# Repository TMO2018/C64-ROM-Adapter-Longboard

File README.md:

# C64-ROM-Adapter-Longboard
Flash ROM replacement for the 24 pol ROMs

The board serves for adapting a CHARACTER (U5, 4k, 2332), KERNAL (U4, 8k, 2364) or BASIC (U3, 8k, 2364) ROM to a 39SF010A (16x8k) / 39SF020A (32x8k) / 39SF040A (64x8k) 5V FLASH-ROM. The pin out of both ICs are slightly different and need adaptation. Furthermore, it allows to access different character sets (up to 32/64/128), kernals (up to 16/32/64) or basics (up to 16/32/64) or a combination of these three ROM typs which can be selected via DIP switch or/and the pin header (A12 to A18) on the module.

The pin header is connected in a way, that the selection can either be accomplished with switches or a microcontroller like an Arduino etc. 

Only one ROM-type (KERNAL or BASIC or CHARACTER) at the same time is allowed.

You can program the FLASH-ROM before soldering or with a special program adaptor after soldering. The second way allows you to reprogram the FLASH-ROM later without resoldering. On the BACK view there are the program pads JA13 to JA18, JWE1 and JOE1.

It should be possible to use the ROM-Adapter in a 1541 floppy drive with 24 pol ROMs (2364) too.

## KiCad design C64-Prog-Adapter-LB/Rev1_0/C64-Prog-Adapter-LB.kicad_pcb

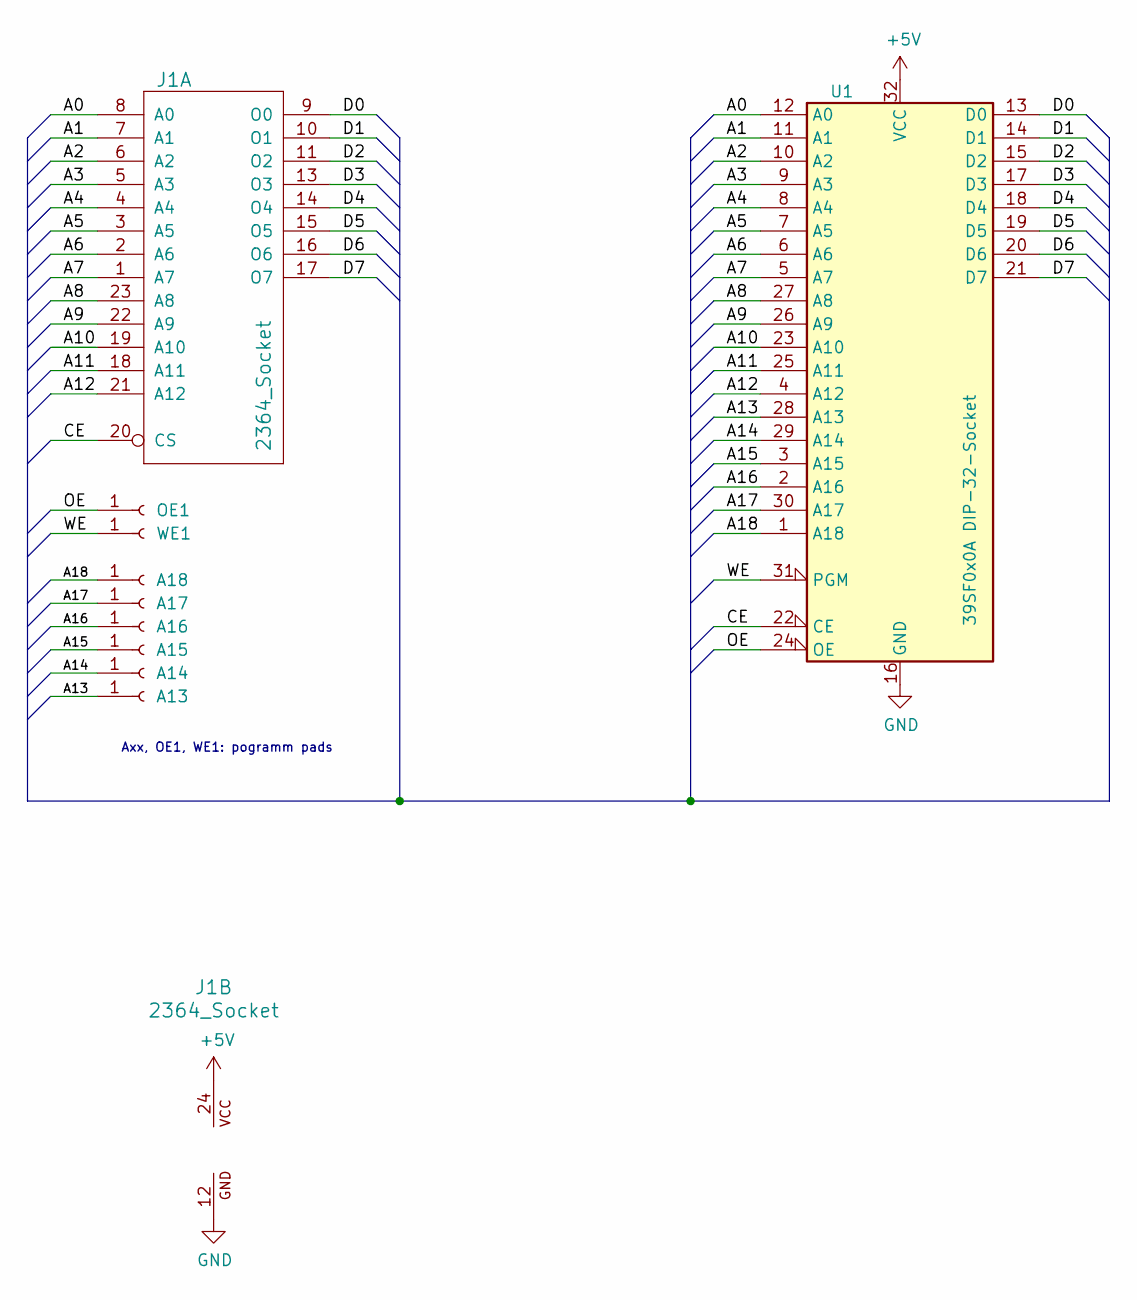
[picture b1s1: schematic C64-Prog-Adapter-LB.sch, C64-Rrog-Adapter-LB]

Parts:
A13, A14, A15, A16, A17, A18: Conn_01x01_Female; Pin_Header_Straight_1x01_Pitch2.54mm_dia1.10mm_TMO
J1: 2364_Socket; DIP-24_2332_2364_Socket
OE1: Conn_01x01_Female; Pin_Header_Straight_1x01_Pitch2.54mm_dia1.10mm_TMO
U1: 39SF0x0A DIP-32-Socket; DIP-32_W15.24mm_Socket_TMO
WE1: Conn_01x01_Female; Pin_Header_Straight_1x01_Pitch2.54mm_dia1.10mm_TMO

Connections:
+5V: J1.24 (VCC), U1.32 (VCC)
/A0: J1.8 (A0), U1.12 (A0)
/A1: J1.7 (A1), U1.11 (A1)
/A2: J1.6 (A2), U1.10 (A2)
/A3: J1.5 (A3), U1.9 (A3)
/A4: J1.4 (A4), U1.8 (A4)
/A5: J1.3 (A5), U1.7 (A5)
/A6: J1.2 (A6), U1.6 (A6)
/A7: J1.1 (A7), U1.5 (A7)
/A8: J1.23 (A8), U1.27 (A8)
/A9: J1.22 (A9), U1.26 (A9)
/A10: J1.19 (A10), U1.23 (A10)
/A11: J1.18 (A11), U1.25 (A11)
/A12: J1.21 (A12), U1.4 (A12)
/A13: A13.1, U1.28 (A13)
/A14: A14.1, U1.29 (A14)
/A15: A15.1, U1.3 (A15)
/A16: A16.1, U1.2 (A16)
/A17: A17.1, U1.30 (A17)
/A18: A18.1, U1.1 (A18)
/CE: J1.20 (CS), U1.22 (CE)
/D0: J1.9 (O0), U1.13 (D0)
/D1: J1.10 (O1), U1.14 (D1)
/D2: J1.11 (O2), U1.15 (D2)
/D3: J1.13 (O3), U1.17 (D3)
/D4: J1.14 (O4), U1.18 (D4)
/D5: J1.15 (O5), U1.19 (D5)
/D6: J1.16 (O6), U1.20 (D6)
/D7: J1.17 (O7), U1.21 (D7)
/OE: OE1.1, U1.24 (OE)
/WE: U1.31 (PGM), WE1.1
GND: J1.12 (GND), U1.16 (GND)

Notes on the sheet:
Axx, OE1, WE1: pogramm pads

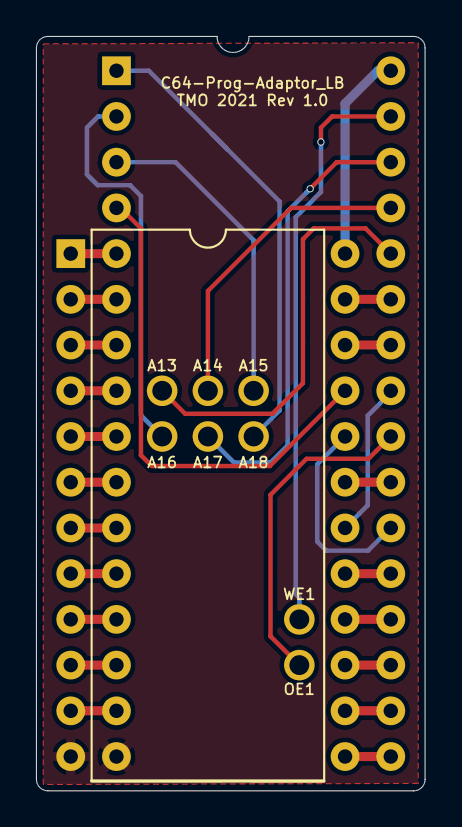
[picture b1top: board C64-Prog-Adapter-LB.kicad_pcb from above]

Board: 2 copper layers, 21.6 x 41.9 mm, 10 parts (0 on the bottom side), 32 nets.

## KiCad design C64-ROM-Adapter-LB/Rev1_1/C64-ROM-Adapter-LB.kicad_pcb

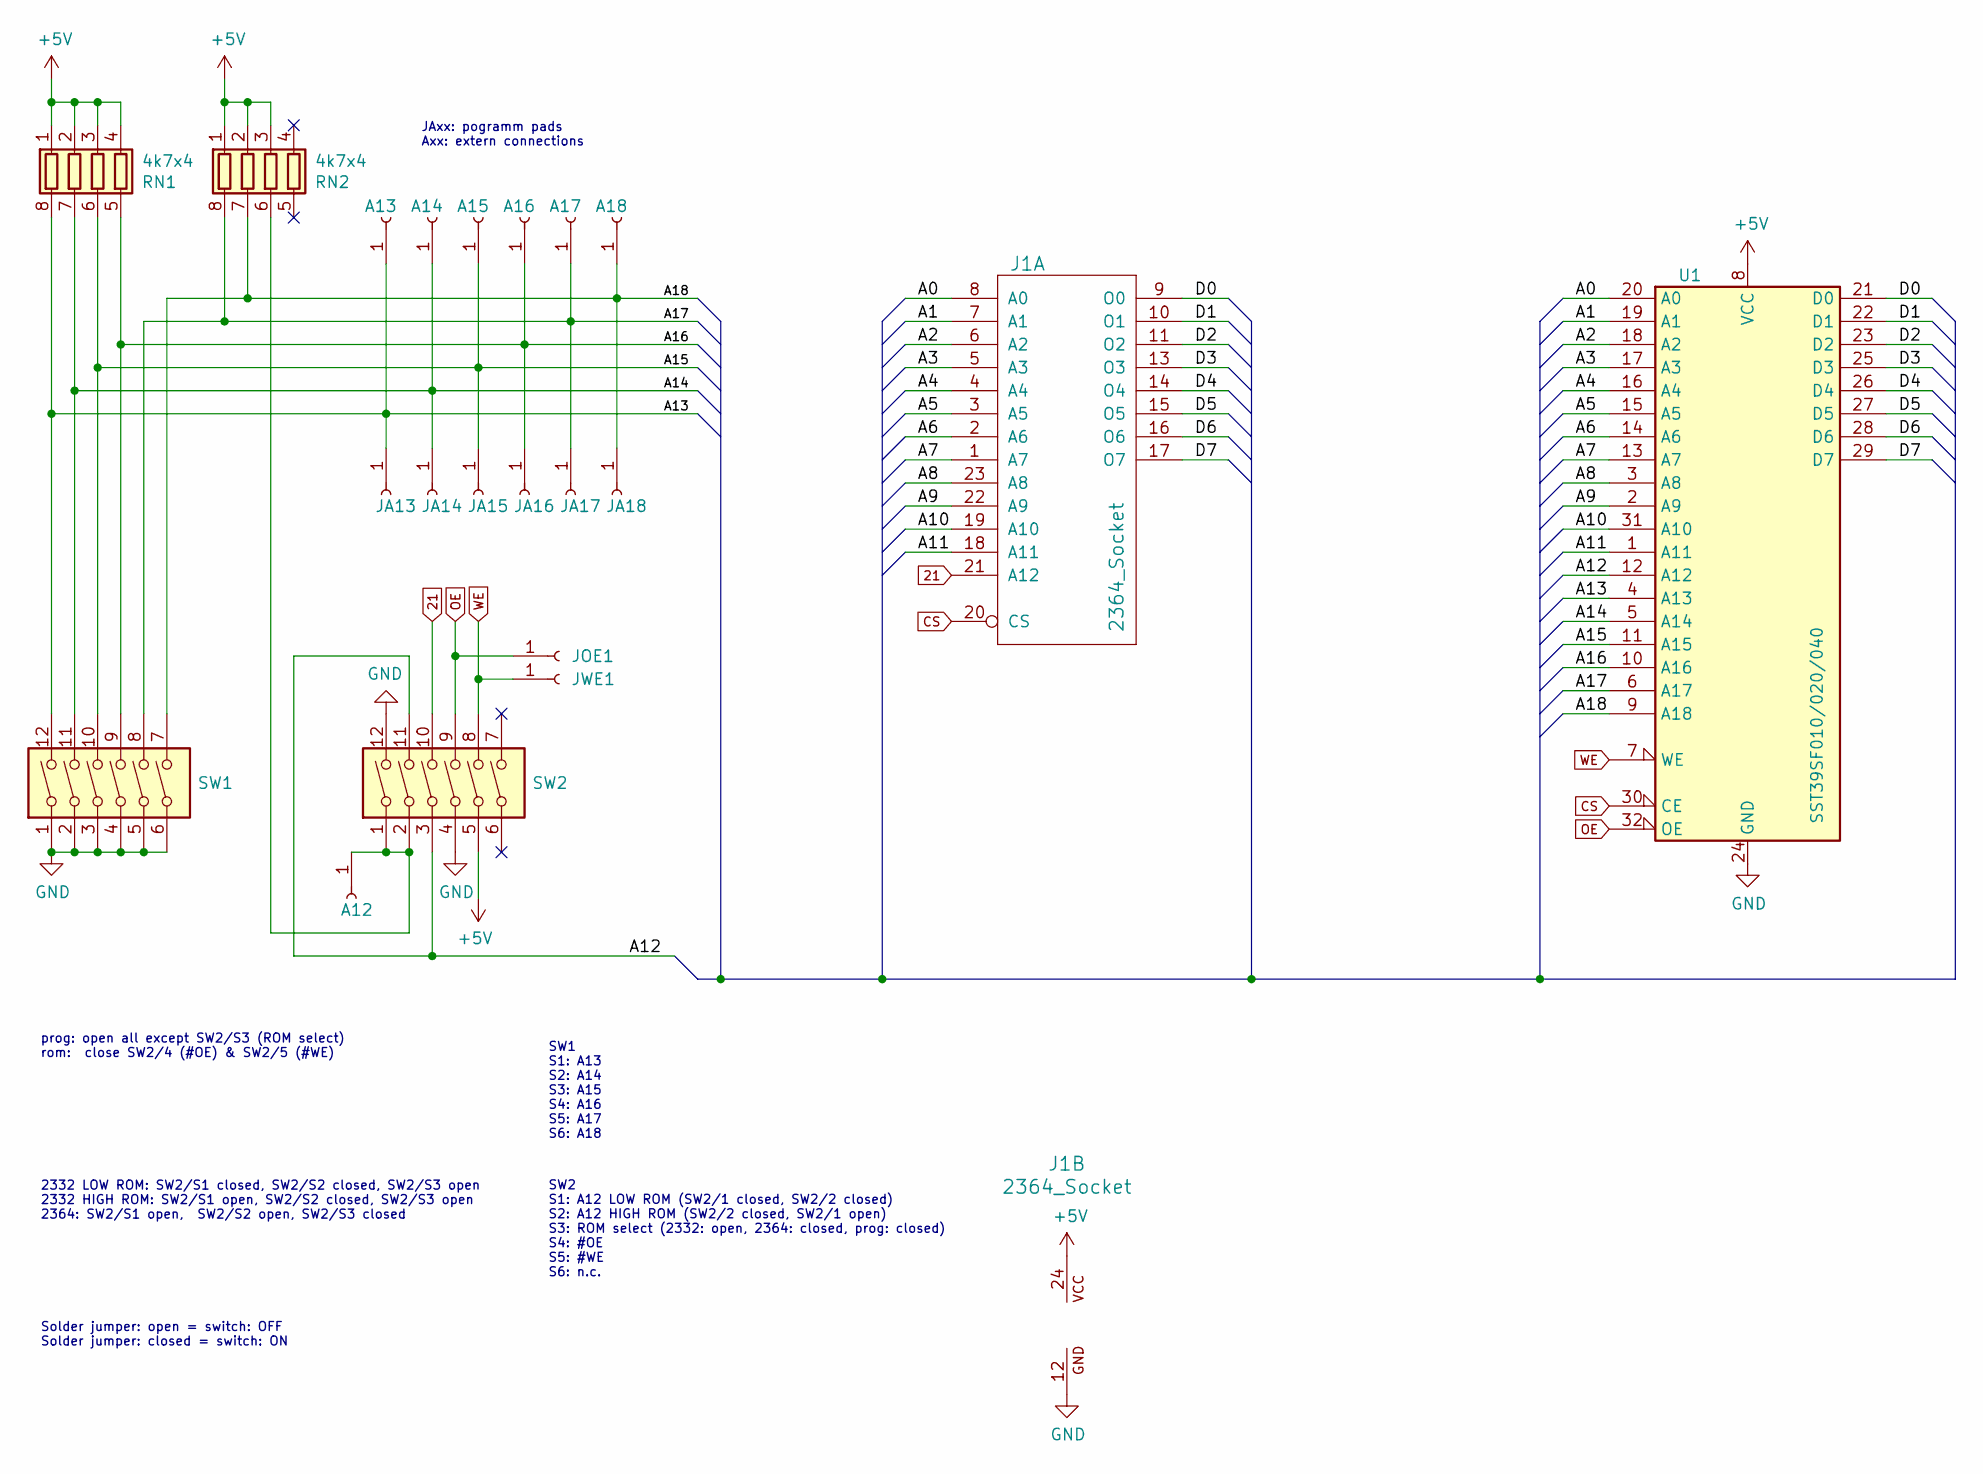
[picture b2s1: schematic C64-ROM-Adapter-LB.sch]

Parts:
A12, A13, A14, A15, A16, A17, A18: Conn_01x01_Female; Pin_Header_Straight_1x01_Pitch2.54mm_TMO
J1: 2364_Socket; DIP-24_2332_2364_Socket
JA13, JA14, JA15, JA16, JA17, JA18: Conn_01x01_Female; Measurement_Point_Round-SMD-Pad_Small
JOE1: Conn_01x01_Female; Measurement_Point_Round-SMD-Pad_Small
JWE1: Conn_01x01_Female; Measurement_Point_Round-SMD-Pad_Small
RN1, RN2: 4k7x4; R_Array_Convex_4x0603
SW1, SW2: SW_DIP_x06; SW_DIP_SPSTx06_DHN_W7.4mm_P1.27mm
U1: SST39SF010/020/040; TSOP-I-32_11.8x8mm_P0.5mm_hand_soldering

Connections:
21: J1.21 (A12), SW2.10
+5V: J1.24 (VCC), RN1.1 (R1.1), RN1.2 (R2.1), RN1.3 (R3.1), RN1.4 (R4.1), RN2.1 (R1.1), RN2.2 (R2.1), RN2.3 (R3.1), SW2.5, U1.8 (VCC)
/A0: J1.8 (A0), U1.20 (A0)
/A1: J1.7 (A1), U1.19 (A1)
/A2: J1.6 (A2), U1.18 (A2)
/A3: J1.5 (A3), U1.17 (A3)
/A4: J1.4 (A4), U1.16 (A4)
/A5: J1.3 (A5), U1.15 (A5)
/A6: J1.2 (A6), U1.14 (A6)
/A7: J1.1 (A7), U1.13 (A7)
/A8: J1.23 (A8), U1.3 (A8)
/A9: J1.22 (A9), U1.2 (A9)
/A10: J1.19 (A10), U1.31 (A10)
/A11: J1.18 (A11), U1.1 (A11)
/A12: SW2.3, SW2.11, U1.12 (A12)
/A13: A13.1, JA13.1, RN1.8 (R1.2), SW1.12, U1.4 (A13)
/A14: A14.1, JA14.1, RN1.7 (R2.2), SW1.11, U1.5 (A14)
/A15: A15.1, JA15.1, RN1.6 (R3.2), SW1.10, U1.11 (A15)
/A16: A16.1, JA16.1, RN1.5 (R4.2), SW1.9, U1.10 (A16)
/A17: A17.1, JA17.1, RN2.8 (R1.2), SW1.8, U1.6 (A17)
/A18: A18.1, JA18.1, RN2.7 (R2.2), SW1.7, U1.9 (A18)
/D0: J1.9 (O0), U1.21 (D0)
/D1: J1.10 (O1), U1.22 (D1)
/D2: J1.11 (O2), U1.23 (D2)
/D3: J1.13 (O3), U1.25 (D3)
/D4: J1.14 (O4), U1.26 (D4)
/D5: J1.15 (O5), U1.27 (D5)
/D6: J1.16 (O6), U1.28 (D6)
/D7: J1.17 (O7), U1.29 (D7)
CS: J1.20 (CS), U1.30 (CE)
GND: J1.12 (GND), SW1.1, SW1.2, SW1.3, SW1.4, SW1.5, SW1.6, SW2.4, SW2.12, U1.24 (GND)
unnamed: A12.1, RN2.6 (R3.2), SW2.1, SW2.2
OE: JOE1.1, SW2.9, U1.32 (OE)
WE: JWE1.1, SW2.8, U1.7 (WE)

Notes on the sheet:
2332 LOW ROM: SW2/S1 closed, SW2/S2 closed, SW2/S3 open 2332 HIGH ROM: SW2/S1 open, SW2/S2 closed, SW2/S3 open 2364: SW2/S1 open, SW2/S2 open, SW2/S3 closed
SW1 S1: A13 S2: A14 S3: A15 S4: A16 S5: A17 S6: A18
prog: open all except SW2/S3 (ROM select) rom: close SW2/4 (#OE) & SW2/5 (#WE)
SW2 S1: A12 LOW ROM (SW2/1 closed, SW2/2 closed) S2: A12 HIGH ROM (SW2/2 closed, SW2/1 open) S3: ROM select (2332: open, 2364: closed, prog: closed) S4: #OE S5: #WE S6: n.c.
JAxx: pogramm pads Axx: extern connections
Solder jumper: open = switch: OFF Solder jumper: closed = switch: ON

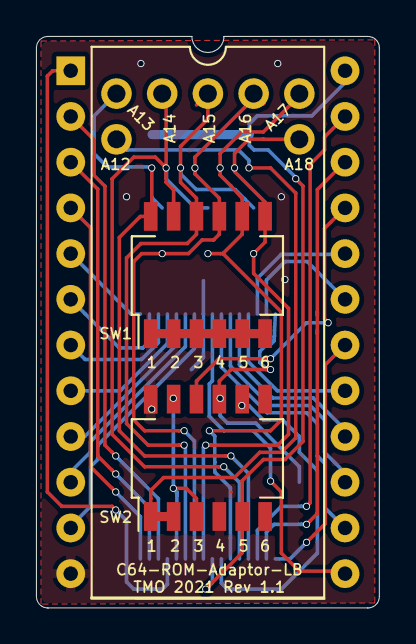
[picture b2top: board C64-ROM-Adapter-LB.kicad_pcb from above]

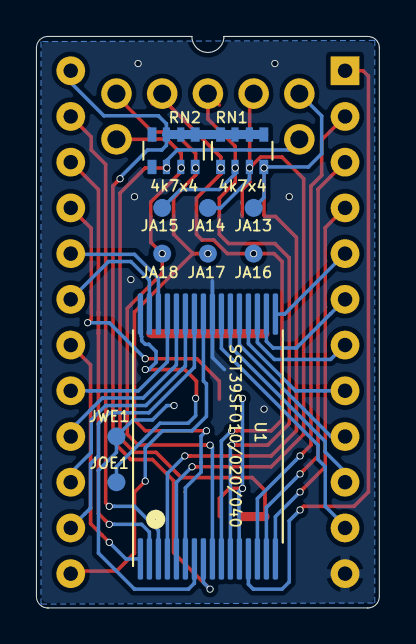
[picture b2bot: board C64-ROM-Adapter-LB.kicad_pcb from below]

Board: 2 copper layers, 19.0 x 31.8 mm, 21 parts (11 on the bottom side), 34 nets.
